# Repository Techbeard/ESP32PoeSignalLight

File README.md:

# ESP32PoeSignalLight
A industial Signal Light

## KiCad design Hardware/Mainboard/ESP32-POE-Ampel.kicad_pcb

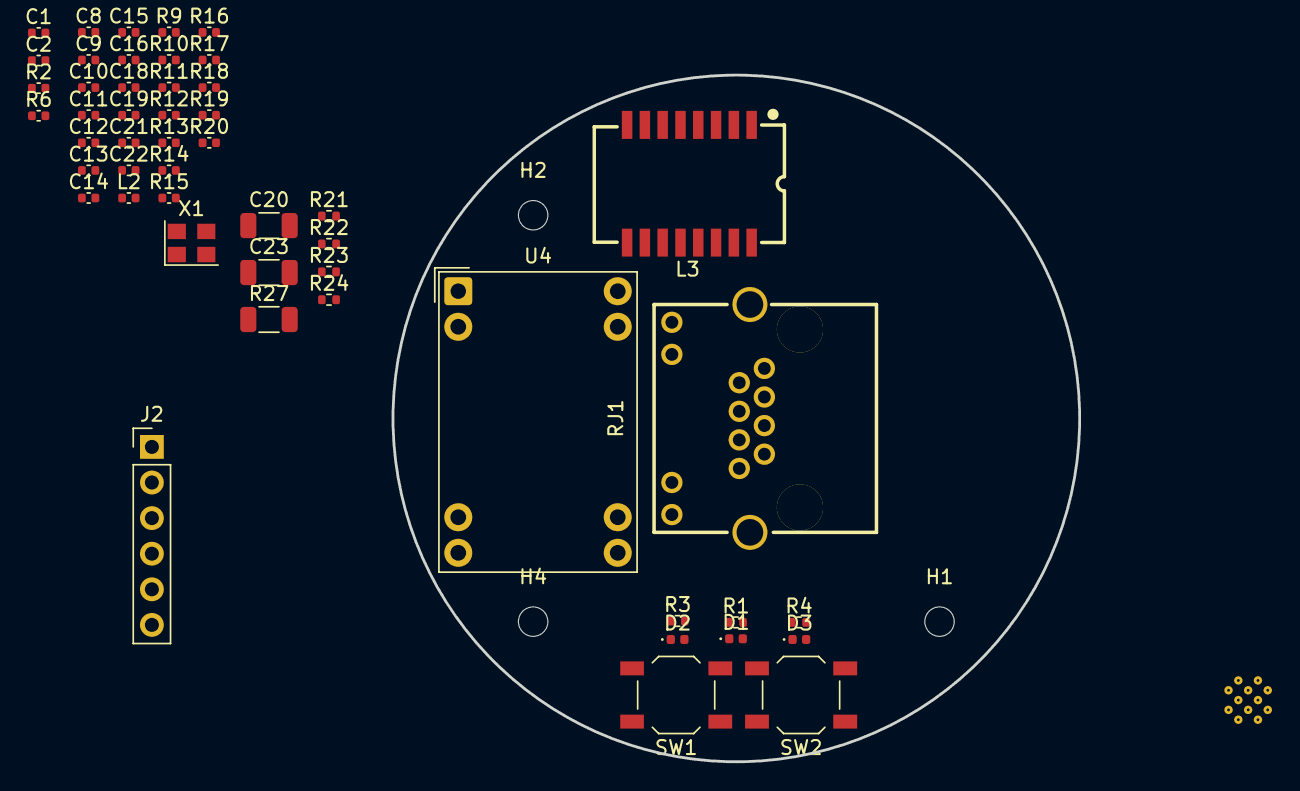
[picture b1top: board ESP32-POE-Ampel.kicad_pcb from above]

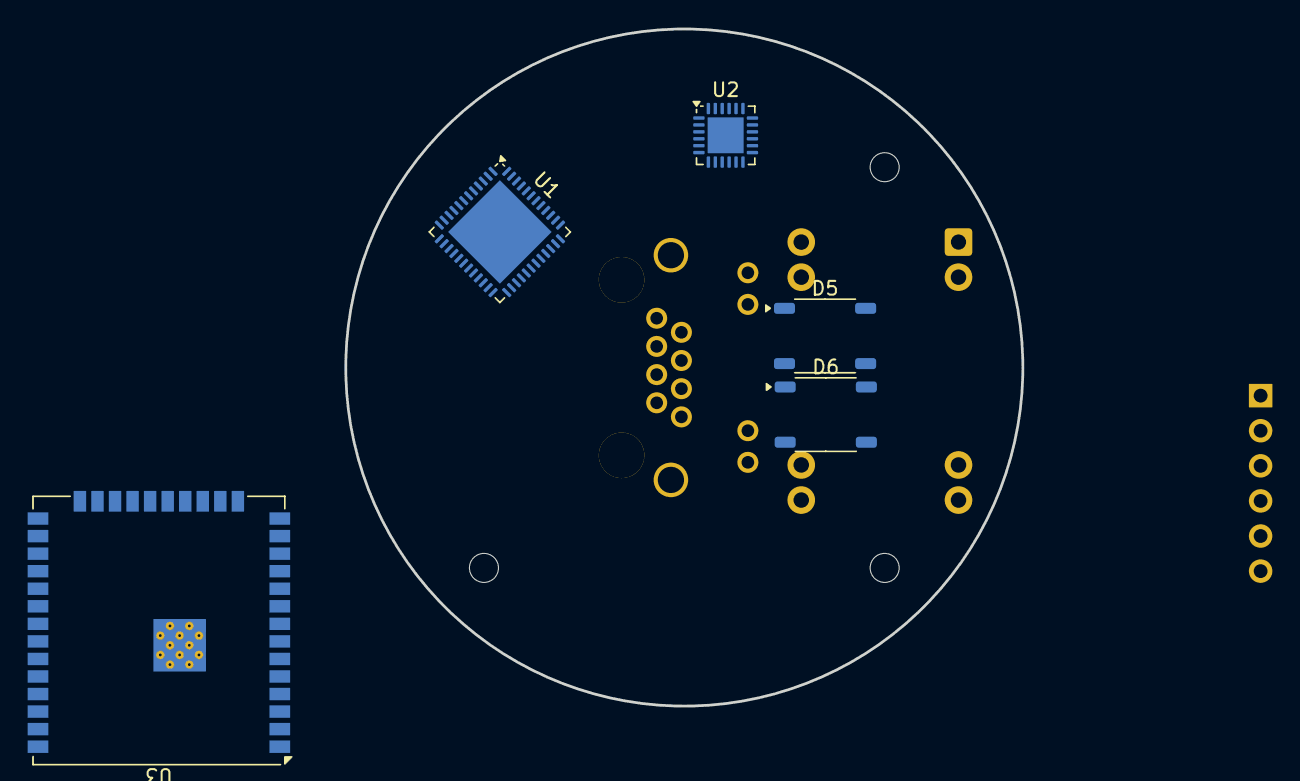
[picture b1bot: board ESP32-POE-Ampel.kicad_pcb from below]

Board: 6 copper layers, 49.0 x 49.0 mm, 58 parts (5 on the bottom side), 55 nets, no tracks yet.

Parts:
C1, C2, C8, C10, C12, C13, C15, C18, C19, C21, C22: 100n; C_0402_1005Metric
C9, C11, C14: 10u; C_0402_1005Metric
C16: NC; C_0402_1005Metric
C20, C23: 1000pF/2KV; C_1206_3216Metric
D1, D2, D3: LED; LED_0402_1005Metric
D5, D6: MDB6S; TSSOP-4_4.4x5mm_P4mm
H1, H2, H4: MountingHole; MountingHole_2.1mm
J2: Conn_01x06_Female; PinHeader_1x06_P2.54mm_Vertical
L2: L_Ferrite; C_0402_1005Metric
L3: B1608S
R1, R3, R4: 1k; R_0402_1005Metric
R2, R6: 4k7; C_0402_1005Metric
R9, R13: 10k; C_0402_1005Metric
R10, R12: 33; C_0402_1005Metric
R11: 1.5k; C_0402_1005Metric
R14, R15: 1k; C_0402_1005Metric
R16: 12k1; C_0402_1005Metric
R17, R18, R19, R20: 49R9; C_0402_1005Metric
R21, R22, R23, R24: 75; R_0402_1005Metric
R27: 0; C_1206_3216Metric
RJ1: R-RJ45R08P-C000; RJ45-TH_R-RJ45R08P-C000
SW1: Reset; SW_SPST_TL3342
SW2: User; SW_SPST_TL3342
U1: ESP32-PICO-D4; QFN-48-1EP_7x7mm_P0.5mm_EP5.3x5.3mm
U2: LAN8720A; QFN-24-1EP_4x4mm_P0.5mm_EP2.6x2.6mm
U3: ESP32-WROOM-32UE
U4: Ag9905LP; Converter_DCDC_Silvertel_Ag99xxLP_THT
X1: ASV-50MHz; Oscillator_SMD_Abracon_ASE-4Pin_3.2x2.5mm

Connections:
+3.3V: RJ1.9 (L+), RJ1.12 (R-)
+3.3VA: C14.1, C15.1, L2.2, L3.2 (TCT), L3.7 (RCT), R17.1, R18.1, R19.1, R20.1, U2.1 (VDD2A), U2.19 (VDD1A)
+3V3: C9.1, C10.1, C13.1, J2.1, L2.1, R2.1, R3.1, R4.1, R6.1, R9.1, R11.1, R13.1, U2.9 (VDDIO), U3.2 (VDD), X1.4 (Vdd)
CLK50M: C16.1, R10.1, R12.1, X1.3 (OUT)
EN: C1.1, J2.6, R2.2, SW1.2, U3.3 (EN)
ETHLEDGreen: R14.2, RJ1.10 (L-)
ETHLEDYel: R15.2, RJ1.11 (R+)
Earth: C20.2, C23.1, R27.1, RJ1.13 (S), RJ1.14 (S)
GND: C1.2, C2.2, C8.2, C9.2, C10.2, C11.2, C12.2, C13.2, C14.2, C15.2, C16.2, C23.2, D1.1 (K), D2.1 (K), J2.2, R16.2, R27.2, SW1.1, SW2.1, U2.25 (VSS), U3.1 (GND), U3.15 (GND), U3.38 (GND), U3.39 (GND), U4.3 (-VDC), X1.2 (GND)
IO0: J2.5, R10.2, U2.14 (INT/REFCLKO), U3.25 (IO0)
IO13_RXER: R9.2, U2.10 (RXER/PHYAD0), U3.16 (IO13)
IO16_OSC_EN: U3.27 (IO16), X1.1 (EN)
IO18_MDIO: R11.2, U2.12 (MDIO), U3.30 (IO18)
IO19_TXD0: U2.17 (TXD0), U3.31 (IO19)
IO21_TXEN: U2.16 (TXEN), U3.33 (IO21)
IO22_TXD1: U2.18 (TXD1), U3.36 (IO22)
IO23_MDC: U2.13 (MDC), U3.37 (IO23)
IO25_RXD0: U2.8 (RXD0/MODE0), U3.10 (IO25)
IO26_RXD1: U2.7 (RXD1/MODE1), U3.11 (IO26)
IO27_CRS_DV: U2.11 (CRS_DV/MODE2), U3.12 (IO27)
unnamed: C18.2, R21.1
unnamed: C19.2, R22.1
unnamed: C20.1, R21.2, R22.2, R23.2, R24.2
unnamed: C21.1, D6.4, RJ1.4, RJ1.5
unnamed: C21.2, R23.1
unnamed: C22.1, D6.3, RJ1.7, RJ1.8
unnamed: C22.2, R24.1
unnamed: D1.2 (A), R1.2
unnamed: D2.2 (A), R3.2
unnamed: D3.2 (A), R4.2
unnamed: D5.1 (+), D6.1 (+), U4.5 (VIN+), U4.6 (VIN+)
unnamed: D5.2 (-), D6.2 (-), U4.7 (VIN-), U4.8 (VIN-)
unnamed: L3.11 (RX+), RJ1.3
unnamed: L3.9 (RX-), RJ1.6
unnamed: C18.1, D5.4, L3.10 (RXCT)
unnamed: L3.16 (TX+), RJ1.1
unnamed: L3.14 (TX-), RJ1.2
unnamed: C19.1, D5.3, L3.15 (TXCT)
unnamed: U1.3 (VDDA3P3), U1.4 (VDDA3P3)
unnamed: U1.1 (VDDA), U1.43 (VDDA), U1.46 (VDDA)
unnamed: R14.1, U2.3 (LED1/REGOFF)
unnamed: R15.1, U2.2 (LED2/nINTSEL)
unnamed: R16.1, U2.24 (RBIAS)
unnamed: C11.1, C12.1, U2.6 (VDDCR)
OSCIN: R12.2, U2.5 (XTAL1/CLKIN)
RX: J2.4, U3.34 (RXD0/IO3)
RXN: L3.8 (RD-), R20.2, U2.22 (RXN)
RXP: L3.6 (RD+), R19.2, U2.23 (RXP)
StateLED: D3.1 (K), U3.28 (IO17)
TX: J2.3, U3.35 (TXD0/IO1)
TXN: L3.3 (TD-), R18.2, U2.20 (TXN)
TXP: L3.1 (TD+), R17.2, U2.21 (TXP)
UserButton: C2.1, R6.2, SW2.2, U3.4 (SENSOR_VP)
VCC: R1.1, U4.1 (+VDC), U4.2 (+VDC)
nRST: C8.1, R13.2, U2.15 (RST)

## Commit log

2024-03-26 add files
